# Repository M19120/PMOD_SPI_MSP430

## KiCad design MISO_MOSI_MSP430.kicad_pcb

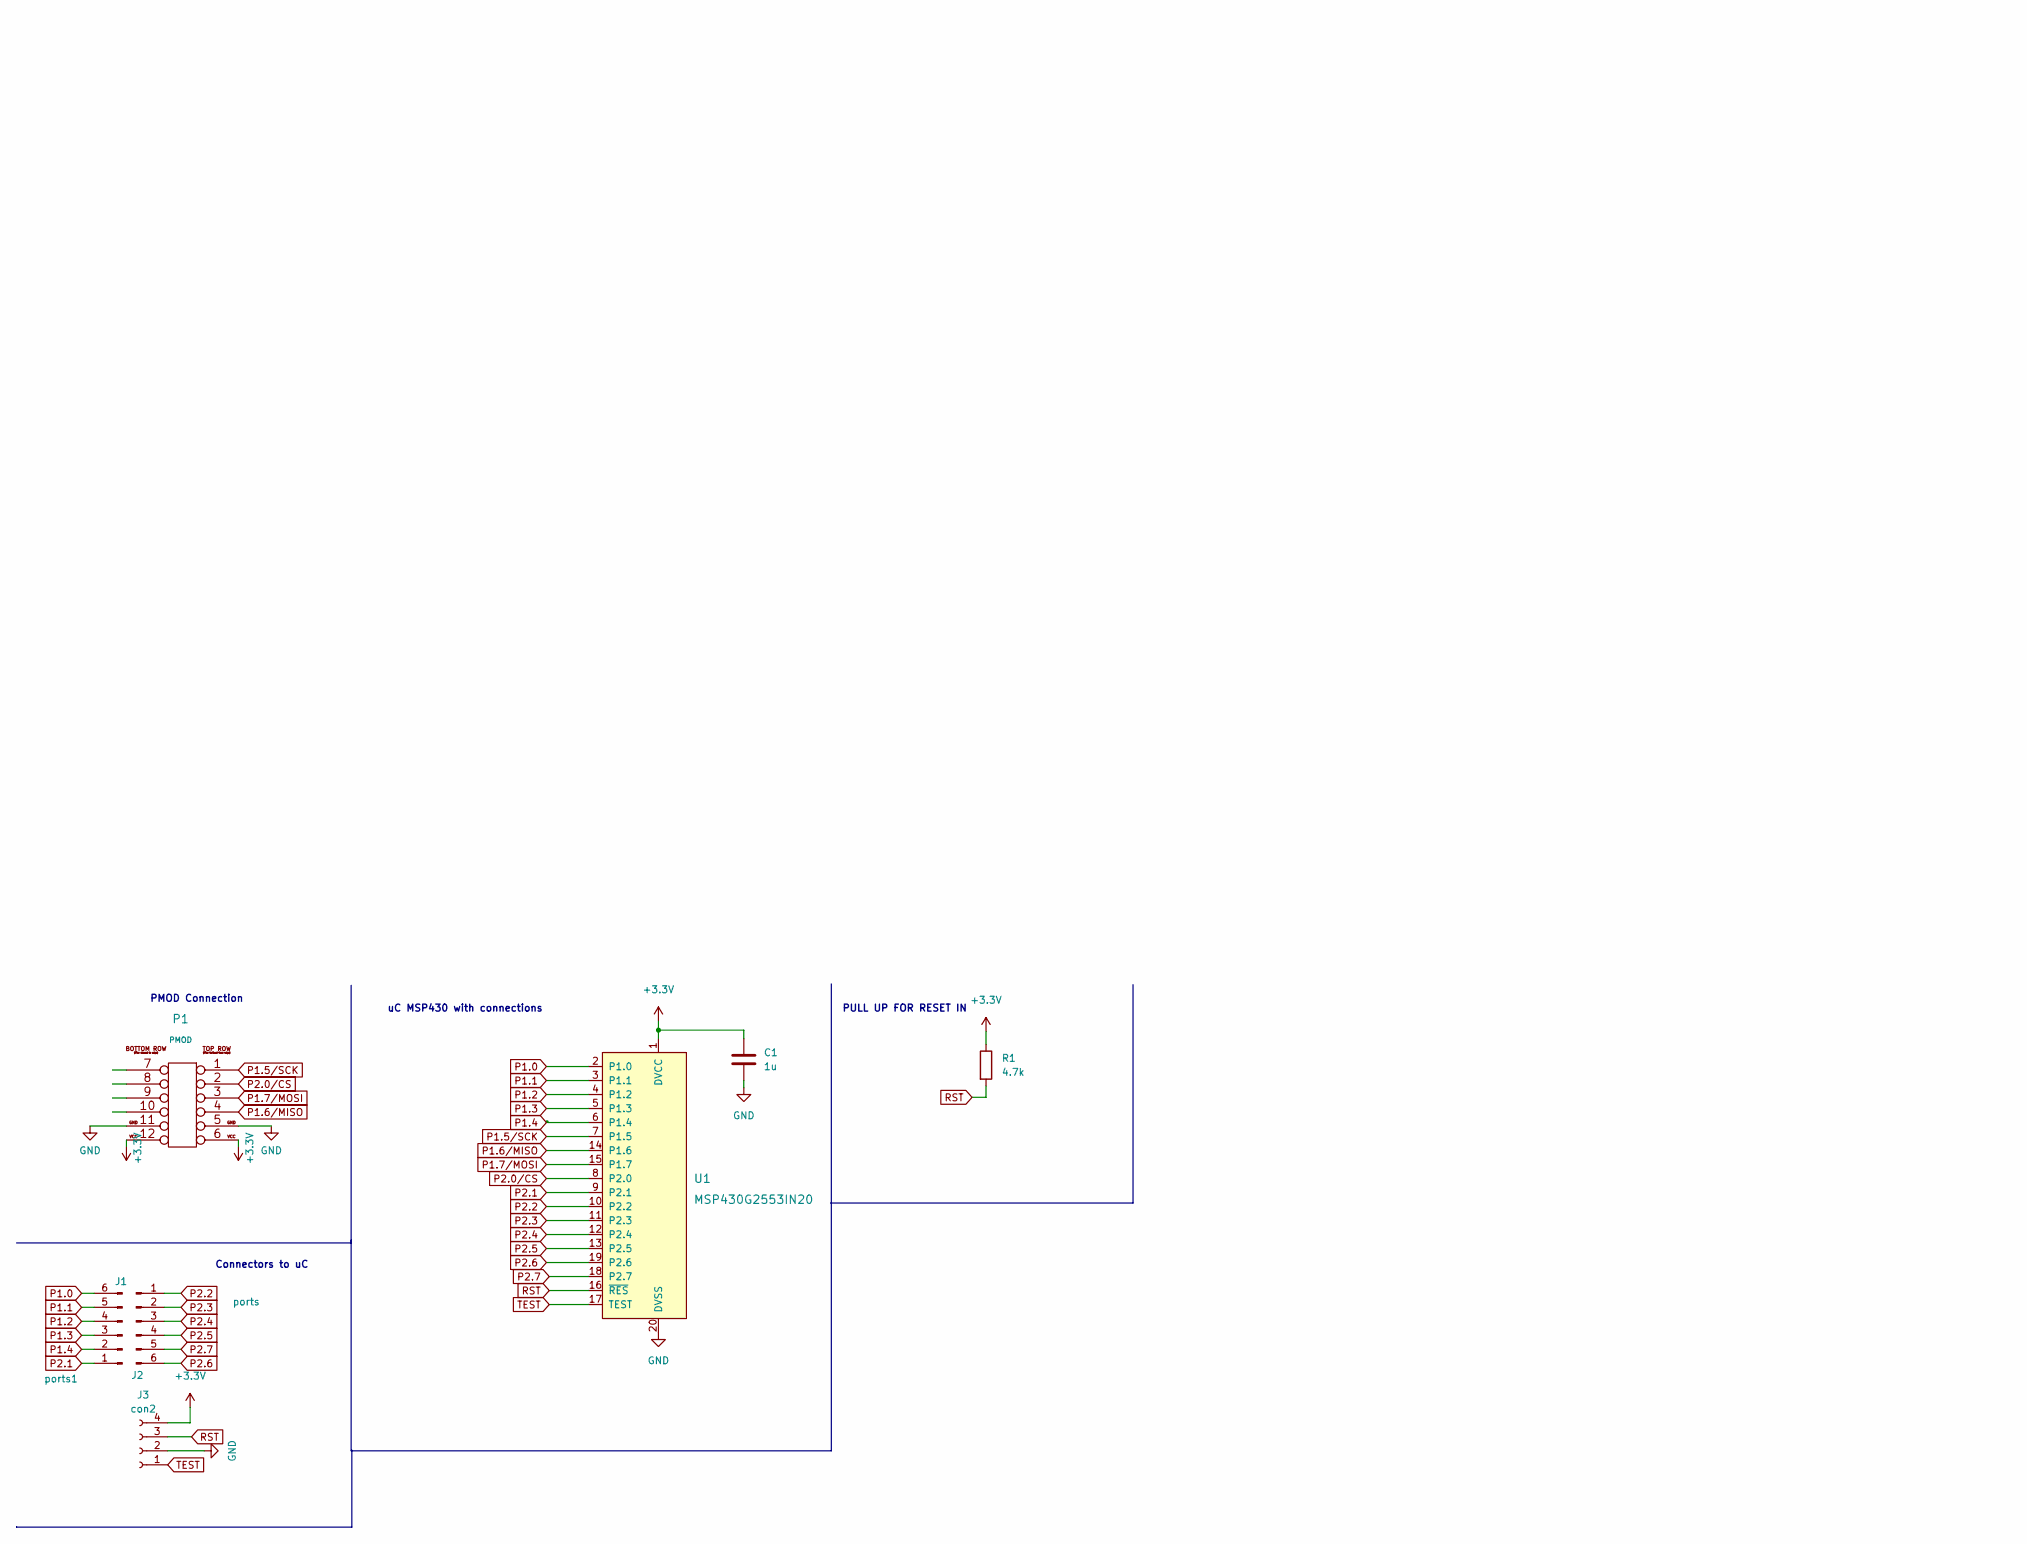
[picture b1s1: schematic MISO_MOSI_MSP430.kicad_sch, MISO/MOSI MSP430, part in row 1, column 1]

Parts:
C1: 1u; CP_Radial_D4.0mm_P1.50mm
J1: ports1; PinHeader_1x06_P2.54mm_Vertical
J2: ports; PinHeader_1x06_P2.54mm_Vertical
J3: con2; PinHeader_1x04_P2.54mm_Vertical
P1: PMOD; pmod_pin_array_6x2
R1: 4.7k; R_Axial_DIN0204_L3.6mm_D1.6mm_P5.08mm_Horizontal
U1: MSP430G2553IN20; DIP-20_W7.62mm; MPN MSP430G2553IN20; Digi-Key_PN 296-28429-5-ND

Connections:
+3V3: C1.1, J3.4, P1.6, P1.12, R1.1, U1.1 (DVCC)
GND: C1.2, J3.2, P1.5, P1.11, U1.20 (DVSS)
P1.0: J1.6, U1.2 (P1.0)
P1.1: J1.5, U1.3 (P1.1)
P1.2: J1.4, U1.4 (P1.2)
P1.3: J1.3, U1.5 (P1.3)
P1.4: J1.2, U1.6 (P1.4)
P1.5/SCK: P1.1, U1.7 (P1.5)
P1.6/MISO: P1.4, U1.14 (P1.6)
P1.7/MOSI: P1.3, U1.15 (P1.7)
P2.0/CS: P1.2, U1.8 (P2.0)
P2.1: J1.1, U1.9 (P2.1)
P2.2: J2.1, U1.10 (P2.2)
P2.3: J2.2, U1.11 (P2.3)
P2.4: J2.3, U1.12 (P2.4)
P2.5: J2.4, U1.13 (P2.5)
P2.6: J2.6, U1.19 (P2.6)
P2.7: J2.5, U1.18 (P2.7)
RST: J3.3, R1.2, U1.16 (~RES)
TEST: J3.1, U1.17 (TEST)

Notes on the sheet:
PMOD Connection
uC MSP430 with connections
PULL UP FOR RESET IN
Connectors to uC

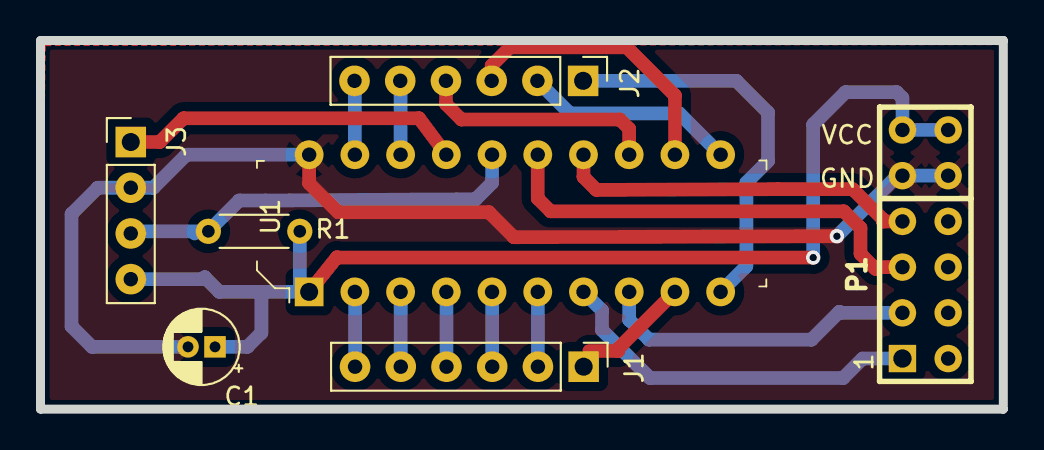
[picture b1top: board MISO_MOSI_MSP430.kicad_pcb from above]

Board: 2 copper layers, 53.5 x 20.5 mm, 7 parts (0 on the bottom side), 20 nets.

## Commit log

2024-09-28 README.md
